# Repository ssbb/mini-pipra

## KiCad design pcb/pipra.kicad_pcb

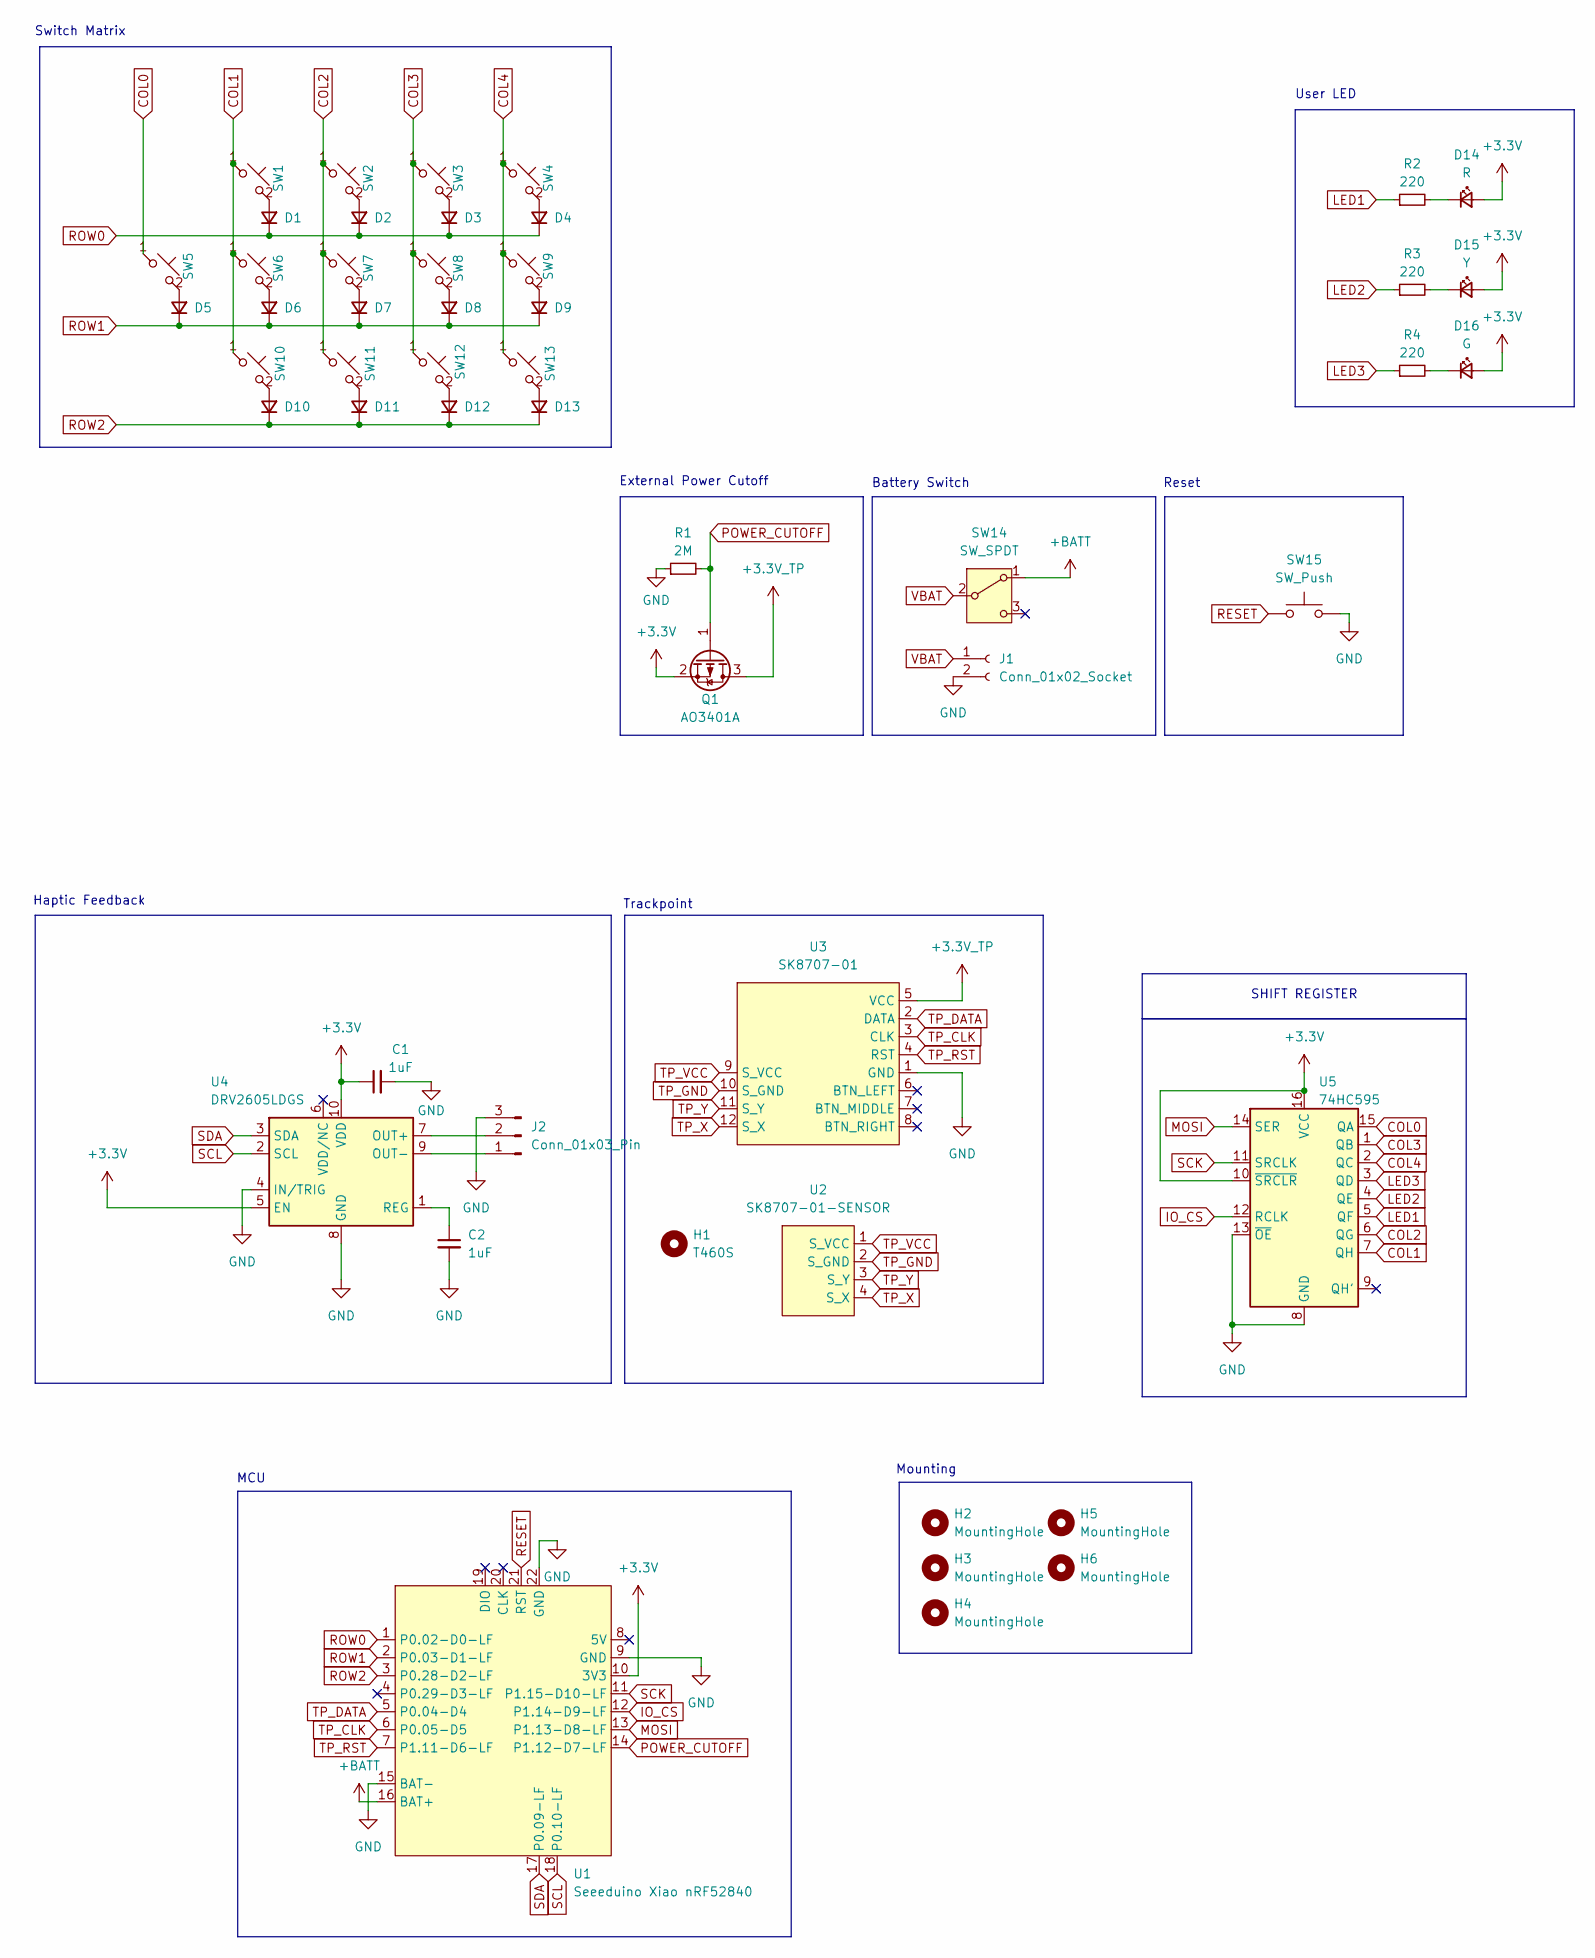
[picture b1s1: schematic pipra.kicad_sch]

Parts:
C1, C2: 1uF; C_1206_3216Metric_reversible
D1, D2, D3, D4, D5, D6, D7, D8, D9, D10, D11, D12, D13: D_Small; D_1206_3216Metric_reversible
D14: R; LED_D3.0mm
D15: Y; LED_D3.0mm
D16: G; LED_D3.0mm
H1: T460S; TP_Lenovo_T460S_Sensor
H2, H3, H4, H5, H6: MountingHole; MountingHole_20
J1: Conn_01x02_Socket; Molex_Pico-EZmate_78171-0002_1x02-1MP_P1.20mm_Vertical_reve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
J2: Conn_01x03_Pin; ELV1411A_reversible
Q1: AO3401A; SOT-23_reversible; LCSC Part Number C15127
R1: 2M; R_1206_3216Metric_reversible; LCSC Part Number C26112
R2, R3, R4: 220; R_1206_3216Metric_reversible
SW1, SW2, SW3, SW4, SW5, SW6, SW7, SW8, SW9, SW10, SW11, SW12, SW13: SW_Push_45deg; SW_Choc_Mini_reversible_1u
SW14: SW_SPDT; SW_SPDT_PCM12_reversible
SW15: SW_Push; Panasonic_EVQPUL_EVQPUC_reversible
U1: Seeeduino Xiao nRF52840; Seed_Studio_XIAO_nRF52840_reversible
U2: SK8707-01-SENSOR; TP_Sensor_Connector_reversible
U3: SK8707-01; TP_Sprintek_SK8707-01_reversible
U4: DRV2605LDGS; VSSOP-10_3x3mm_P0.5mm_reversible
U5: 74HC595; TSSOP-16_4.4x5mm_P0.65mm_reversible

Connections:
+3.3V: C1.1, D14.2 (A), D15.2 (A), D16.2 (A), Q1.2 (S), U1.10 (3V3), U4.5 (EN), U4.10 (VDD), U5.10 (~SRCLR), U5.16 (VCC)
+3.3V_TP: Q1.3 (D), U3.5 (VCC)
+BATT: SW14.1 (A), U1.16 (BAT+)
COL0: SW5.1, U5.15 (QA)
COL1: SW1.1, SW6.1, SW10.1, U5.7 (QH)
COL2: SW2.1, SW7.1, SW11.1, U5.6 (QG)
COL3: SW3.1, SW8.1, SW12.1, U5.1 (QB)
COL4: SW4.1, SW9.1, SW13.1, U5.2 (QC)
GND: C1.2, C2.2, J1.2, J2.3, R1.1, SW15.2, U1.9 (GND), U1.15 (BAT-), U1.22 (GND), U3.1 (GND), U4.4 (IN/TRIG), U4.8 (GND), U5.8 (GND), U5.13 (~OE)
IO_CS: U1.12 (P1.14-D9-LF), U5.12 (RCLK)
LED1: R2.1, U5.5 (QF)
LED2: R3.1, U5.4 (QE)
LED3: R4.1, U5.3 (QD)
MOSI: U1.13 (P1.13-D8-LF), U5.14 (SER)
unnamed: D1.2 (A), SW1.2
unnamed: D2.2 (A), SW2.2
unnamed: D3.2 (A), SW3.2
unnamed: D4.2 (A), SW4.2
unnamed: D5.2 (A), SW5.2
unnamed: D6.2 (A), SW6.2
unnamed: D7.2 (A), SW7.2
unnamed: D8.2 (A), SW8.2
unnamed: D9.2 (A), SW9.2
unnamed: D10.2 (A), SW10.2
unnamed: D11.2 (A), SW11.2
unnamed: D12.2 (A), SW12.2
unnamed: D13.2 (A), SW13.2
unnamed: D14.1 (K), R2.2
unnamed: D15.1 (K), R3.2
unnamed: D16.1 (K), R4.2
unnamed: J2.1, U4.9 (OUT-)
unnamed: J2.2, U4.7 (OUT+)
unnamed: C2.1, U4.1 (REG)
POWER_CUTOFF: Q1.1 (G), R1.2, U1.14 (P1.12-D7-LF)
RESET: SW15.1, U1.21 (RST)
ROW0: D1.1 (K), D2.1 (K), D3.1 (K), D4.1 (K), U1.1 (P0.02-D0-LF)
ROW1: D5.1 (K), D6.1 (K), D7.1 (K), D8.1 (K), D9.1 (K), U1.2 (P0.03-D1-LF)
ROW2: D10.1 (K), D11.1 (K), D12.1 (K), D13.1 (K), U1.3 (P0.28-D2-LF)
SCK: U1.11 (P1.15-D10-LF), U5.11 (SRCLK)
SCL: U1.18 (P0.10-LF), U4.2 (SCL)
SDA: U1.17 (P0.09-LF), U4.3 (SDA)
TP_CLK: U1.6 (P0.05-D5), U3.3 (CLK)
TP_DATA: U1.5 (P0.04-D4), U3.2 (DATA)
TP_GND: U2.2 (S_GND), U3.10 (S_GND)
TP_RST: U1.7 (P1.11-D6-LF), U3.4 (RST)
TP_VCC: U2.1 (S_VCC), U3.9 (S_VCC)
TP_X: U2.4 (S_X), U3.12 (S_X)
TP_Y: U2.3 (S_Y), U3.11 (S_Y)
VBAT: J1.1, SW14.2 (B)

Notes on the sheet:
Trackpoint
Battery Switch
Haptic Feedback
Reset
SHIFT REGISTER
MCU
Switch Matrix
User LED
Mounting
External Power Cutoff

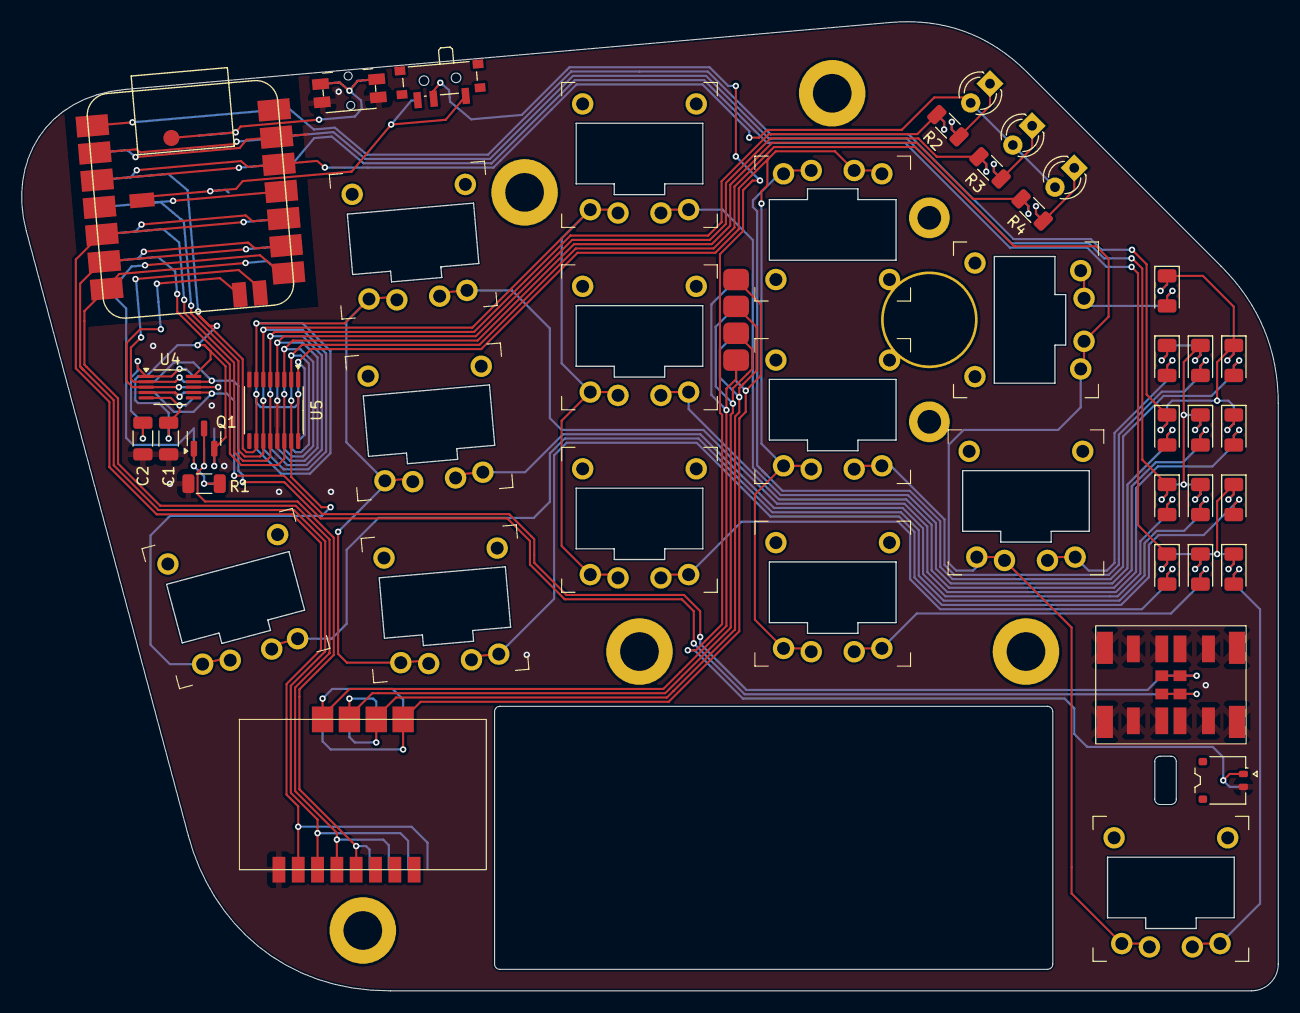
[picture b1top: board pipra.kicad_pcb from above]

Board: 2 copper layers, 117.0 x 90.2 mm, 52 parts (0 on the bottom side), 49 nets.

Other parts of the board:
H7: Bottom Plate; BottomPlate

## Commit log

2024-07-29 Add schematic
2024-07-29 Add schematic labels on mcu
2024-08-22 Prepare pcb
2024-08-22 Add pcb outline
2024-08-22 Place test xiao footprint
2024-08-22 Remove pullup resistors and reset circuit
2024-08-24 Adjust main components placement
2024-08-24 Place diodes
2024-08-24 Re-arrange diodes
2024-08-24 Pre-expirement changes
2024-08-24 Relocate haptic motor
2024-08-24 Start back with e73 module
2024-08-25 Assign footprints
2024-08-26 wip arrange
2024-08-27 Wire everything except the mcu
2024-08-27 Wire shift register
2024-08-27 Finish wiring
2024-08-27 Ordered
2024-10-01 Finish edge cuts
2024-10-01 Got good arrangement
2024-10-08 Basic routing and diodes routing
2024-10-10 Good progsess on tracks
2024-10-12 Route haptic driver
2024-10-13 Almost routed, changing 595 package
2024-10-15 Good progress on routing
2024-10-15 Use in-house footprints,
2024-10-18 Almost done!
2024-10-18 Before breaking everything
2024-10-18 Ready to go!
2024-10-18 Add hatch pattern
2024-10-18 Add reference designators
2024-10-19 WIP plates
2024-10-19 order!
2024-10-26 After order
